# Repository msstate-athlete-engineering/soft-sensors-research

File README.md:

# MSU Soft Sensors Research #
Tools created and maintained by MSU Athlete Engineering research concerning soft robotic sensors (SRSs).

## Items and Descriptions ##
* **gait-biomechanics-tools** - Python and R scripts developed to preprocess and analyze MOCAP/SRS experimental data.
* **SSTK-labkit-v1** - Hardware design files, firmware source, and documentation for assembly/use of SSTK-labkit-v1 modules.
* **SSTK-lab-manager** - Graphical user interface implemented in Python with Qt5 to interface to SSTK-labkit modules and facilitate lab data collection.

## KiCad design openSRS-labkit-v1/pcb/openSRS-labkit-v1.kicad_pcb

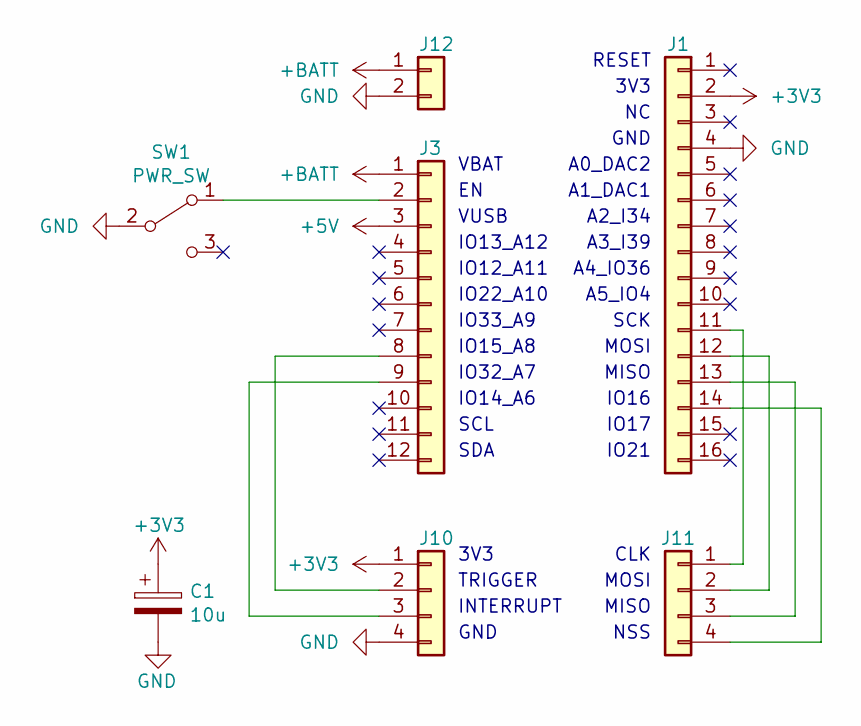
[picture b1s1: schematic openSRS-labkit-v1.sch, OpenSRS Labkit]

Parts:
C1: 10u
J1: Conn_01x16; PinHeader_1x16_P2.54mm_Vertical
J3: Conn_01x12; PinHeader_1x12_P2.54mm_Vertical
J10, J11: Conn_01x04; PinHeader_1x04_P2.54mm_Vertical
J12: Conn_01x02; PinHeader_1x02_P2.54mm_Vertical
SW1: PWR_SW; PinHeader_1x03_P2.54mm_Vertical

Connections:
+3V3: C1.1, J1.2, J10.1
+5V: J3.3
+BATT: J3.1, J12.1
GND: C1.2, J1.4, J10.4, J12.2, SW1.2 (B)
unnamed: J1.11, J11.1
unnamed: J1.12, J11.2
unnamed: J1.13, J11.3
unnamed: J1.14, J11.4
unnamed: J3.2, SW1.1 (A)
unnamed: J3.8, J10.2
unnamed: J3.9, J10.3

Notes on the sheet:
VBAT
VUSB
IO13_A12
IO12_A11
IO22_A10
IO33_A9
IO15_A8
IO32_A7
IO14_A6
SCL
SDA
RESET
3V3
GND
A0_DAC2
A1_DAC1
A2_I34
A3_I39
A4_IO36
A5_IO4
SCK
MOSI
MISO
IO16
IO17
IO21
TRIGGER
INTERRUPT
CLK
NSS

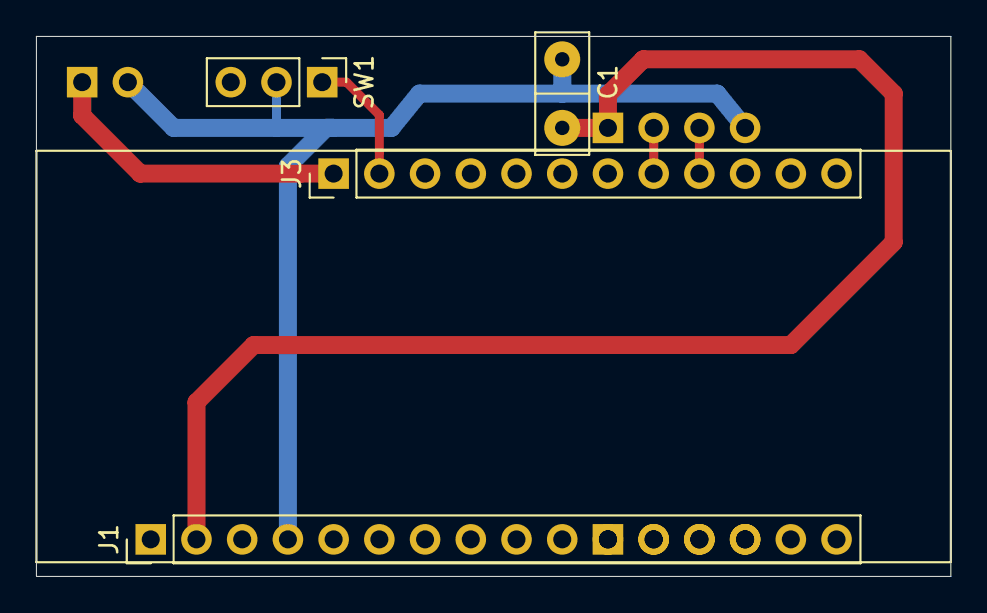
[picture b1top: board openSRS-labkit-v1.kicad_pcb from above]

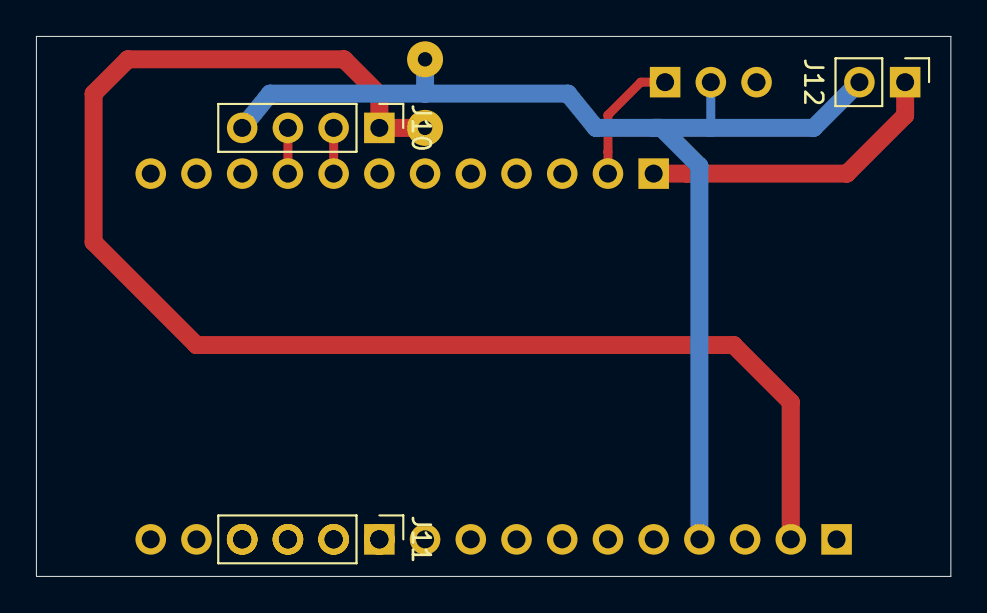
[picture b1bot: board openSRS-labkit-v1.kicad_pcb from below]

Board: 2 copper layers, 50.8 x 30.0 mm, 7 parts (3 on the bottom side), 10 nets.

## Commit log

2020-08-04 created placeholder directories
2020-08-04 added datasets directory placeholder
2022-04-20 Adding README and SRS lab kit tools for Release-001
2022-04-20 Adding Closing the Wearable Gap Parts II and IV analysis for Release-001
2022-04-20 Adding CtWG Parts VI and VIII and other files for Release-001
    Also including utility scripts folder (to be expanded upon in future revisions) and added .gitignore
2022-04-20 Adding CtGW Part IX analysis for Release-001
2022-04-20 Adding CtGW Part IX preprocessed data for Release-001
2022-04-20 Adding CtWG Parts II and IV datasets for Release-001
2022-04-20 Adding CtWG Parts VI and VIII Datasets for Release-001
2022-04-20 Adding CtWG Part IX Dataset for Release-001
